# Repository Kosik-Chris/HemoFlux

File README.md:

# HemoFlux
Wearable Photoplethysmography for blood flow analysis.

Example Streaming of Red, Infrared, and green wavelength values to Note 9 Android device:

## Introduction
The Aim of this project is to create a pseudo realtime embedded device for streaming of sensor values to a smart phone or computer (referred to as client).

The device is intended to be placed on patients extremity with premapped PPG node locations and perform sensor fusion for feature extraction focused on determining blood flow and correlated data.

## Implementation

The Primary Mechanism for acheiving this is Bluetooth Low Energy with our embedded device running as the server allowing various clients to connect. The device also supports 2.4GHz wifi for future extensions.

The mobile application is currently implemented through **React Native** (NON EXPO). The Firmware is currently implemented using Arduino Core, with provided SparkFun Library for I2C communication with MAX3010X chips. 

How to install:

Partitioned into 3 segments: board files (easy eda source), ESP32 firmware, Xplat mobile app

### How to install mobile app:

1. Open HemoFlux folder under mobile
2. Install react-native-cli https://www.npmjs.com/package/react-native-cli
3. (recommended) install yarn
4. run npm i/ yarn from root
5. run react-native start from root and react-native run-android
6. Ensure to check your permissions on your phone before running.

### How to install firmware:

1. Open HemoFlux.ino under /firmware/HemoFlux
2. Install I2Cdev as a library
3. **IMPORTANT** currently modified part of the Arduino Core for ESP32 package => BLECharacteristic.cpp. All that is modified is the reversing of the order of bytes set. Will change this in future updates so the client will interpret but this was the "prototype quick solution". The modified file is included in the documents folder.

### Hardware setup

This is (currently) a very very easy project to implement on your breadboard and get working. Additionally, see the schematics under board directory for details.

### Further Aims of this project

1. Animate and annotate a 3D model to realize better blood flow feature extraction

### Current issues/work

1. React Native RAM consumption is dangerously high, performance issues for real time streaming. Performance analysis (starting with code/ algorithm implementation) is the starting point for further work.
2. Fixing working file output/ app local information
3. Implementing feature extraction Matlab work into javascript/ C code
4. Refactoring main BLE streaming into graph code into maintainable format.
5. Continued hardware debugging, currently random disconnects while running firmware.
6. Migration away from Arduino to Espressif, possible migration from React Native to purely native applications.

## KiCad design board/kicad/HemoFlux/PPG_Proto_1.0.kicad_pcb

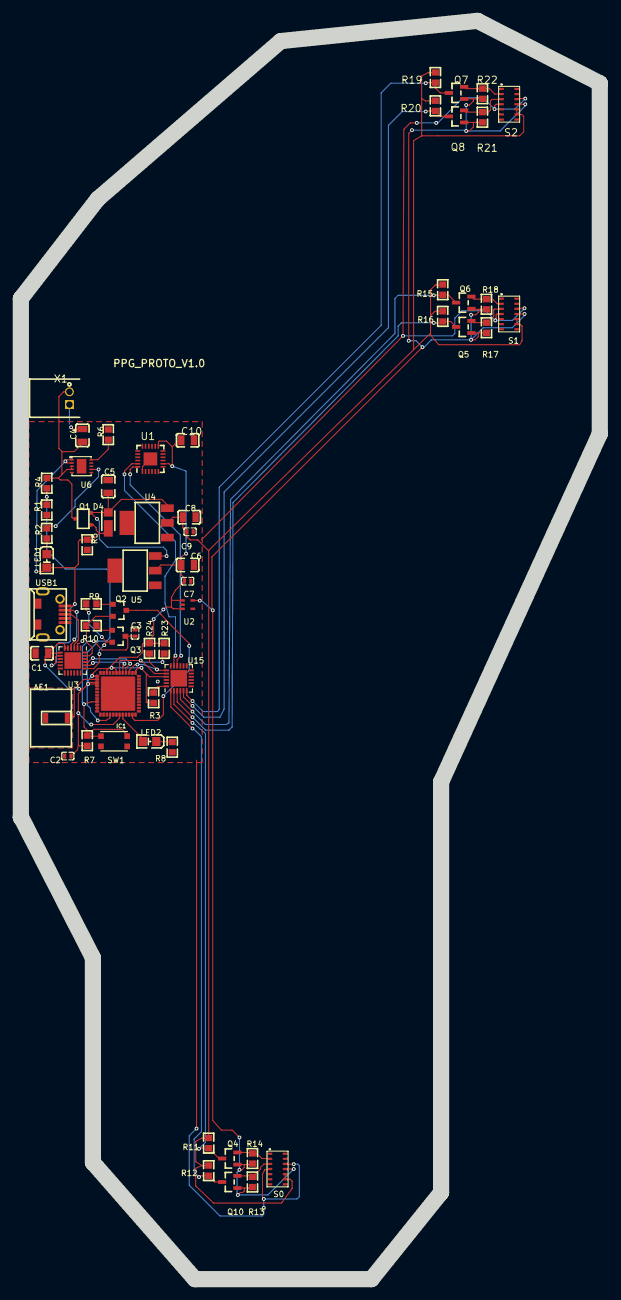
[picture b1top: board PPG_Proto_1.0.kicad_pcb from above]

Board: 2 copper layers, 90.8 x 197.4 mm, 61 parts (0 on the bottom side), 41 nets.

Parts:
AE1: AMCA31-2R450G-S1F-T3; AMCA31-2R450G-S1F-T3.PACK
C1, C4, C5, C6, C8, C10: 10uF; C0805
C2, C3, C7, C9: 1uF; C0402
D4: MBR120; SOD-123HE_L2.8-W1.8-LS3.7-RD
IC1: ESP32-PICO-V4; QFN48
LED1, LED2: SZYY0805YG --GREEN LED; LED0805-R-RD
Q1: DMP2045U-7; SOT-23F
Q2, Q3: MMBT2222ALT1; SOT23-3
Q4, Q5, Q6, Q7, Q8, Q10: 2N7002LT1G; SOT-23_L2.9-W1.3-P0.95-LS2.4-BR
R1, R4, R5: 100K; R0603
R2, R3, R6, R7, R8, R9, R10: 10K; R0603
R11, R12, R13, R14, R15, R16, R17, R18, R19, R20, R21, R22, R23, R24: 4.7K; R0603
S0, S1, S2: MAX30105SMD; OLGA-14
SW1: KMR2; BTN_KMR2_4.6X2.8
U1: MPU6050; QFN50P400X400X95-25T265X275N
U2: TLV70018DCKR; SC70
U3: CP2104; QFN-24-1EP_4X4MM_PITCH0.5MM
U4: ADP3338AKCZ-5-R7; SOT-223
U5: ADP3338AKCZ-3.3RL7; SOT-223
U6: MCP73223-C2SI/MF COPY; TDFN-10_L3.0-W3.0-P0.50-BL-EP
U15: TCA9548A_QFN; QFN-24-1EP_4X4MM_PITCH0.5MM
USB1: MICRO USB 5S B; MICRO-USB-1
X1: S2B-PH-K-S(LF)(SN)

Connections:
+1.8V: Q4.1, Q5.1, Q6.1, Q7.1, Q8.1, Q10.1, R13.2, R14.2, R17.2, R18.2, R21.2, R22.2, S0.11, S1.11, S2.11, U2.5
+3.3V: C1.1, C2.2, C6.1, C7.2, C10.1, IC1.1, IC1.3, IC1.4, IC1.19, IC1.37, IC1.43, IC1.46, R3.1, R7.2, R23.2, R24.2, U1.8, U1.13, U2.1, U2.3, U3.5, U3.6, U3.7, U5.2, U15.21
+5V: C8.2, C9.2, R11.2, R12.2, R15.2, R16.2, R19.2, R20.2, S0.9, S0.10, S1.9, S1.10, S2.9, S2.10, U4.2
BUS_SCL: IC1.39, R24.1, U15.19
BUS_SDA: IC1.42, R23.1, U15.20
D+: U3.3, USB1.3
D-: U3.4, USB1.2
DTR: Q2.2, R10.1, U3.23
GND: C1.2, C2.1, C3.1, C4.1, C5.1, C6.2, C7.1, C8.1, C9.1, C10.2, R1.1, R5.1, R6.1, R8.1, S0.4, S0.12, S1.4, S1.12, S2.4, S2.12, SW1.A, SW1.A', U1.1, U1.9, U1.11, U1.18, U1.25, U2.2, U3.2, U4.1, U5.1, U6.8, U6.9, U6.11, U15.9, U15.18, U15.22, U15.23, USB1.5, X1.1
IO0: IC1.23, Q2.3
IO13: IC1.20, LED2.1
LNA_IN: AE1.S, IC1.2
LV_SCL0: Q4.2, R14.1, S0.2
LV_SCL1: Q6.2, R18.1, S1.2
LV_SCL2: Q7.2, R22.1, S2.2
LV_SDA0: Q10.2, R13.1, S0.3
LV_SDA1: Q5.2, R17.1, S1.3
LV_SDA2: Q8.2, R21.1, S2.3
Q2_1: Q2.1, R9.2
Q3_1: Q3.1, R10.2
R2_1: LED1.2, R2.1
R2_2: R2.2, U6.7
R6_2: R6.2, U6.10
R8_2: LED2.2, R8.2
RESET: C3.2, IC1.9, Q3.3, R7.1, SW1.B, SW1.B'
RTS: Q3.2, R9.1, U3.19
RXD: IC1.40, U3.21
SCL0: Q4.3, R11.1, U15.2
SCL1: Q6.3, R15.1, U15.4
SCL2: Q7.3, R19.1, U15.6
SCL7: U1.23, U15.17
SDA0: Q10.3, R12.1, U15.1
SDA1: Q5.3, R16.1, U15.3
SDA2: Q8.3, R20.1, U15.5
SDA7: U1.24, U15.16
TXD: IC1.41, U3.20
U15_24: R3.2, U15.24
VBAT: C4.2, Q1.3, R4.2, U6.3, U6.4, X1.2
VBAT_REC: C5.2, D4.2, Q1.2, U4.3, U5.3
VBAT_SENSE: IC1.16, R1.2, R4.1
VBUS: D4.1, LED1.1, Q1.1, R5.2, U3.8, U6.1, U6.2, USB1.1

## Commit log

2020-02-24 Init
2020-02-24 Hardware files upload
2020-02-24 Swap over misc sketches into central repo
2020-02-24 Working App update. TODO (x2): 1. Acquire and measure BLE readings 2. Test on ios/ that yarn is working for node env
2020-03-06 Android Icon update
2020-03-08 Working on BLE ingest
2020-03-09 Firmware + BLE tx updates. Removed RTOS from PPG sys as unstable/ dropping of tasks. PPG_SYS.ino is main firmware file. App in basic receive functionality with UI rendering for 1 characteristic
2020-03-09 Added battery tx and changed pin to ADC1 GPIO 34
2020-03-11 IOS updates
2020-03-18 New Board design. Updated documentation.
2020-03-19 Mobile app render single line graph value. Determined timing sensitivities for UI response requires lower frequency update rates to notifications. Active firmware is HemoFlux, not PPG RTOS. TODO: upd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
2020-03-20 variable ppg support. IMU in progress. Exception handling
2020-03-23 Firmware updates: Added IMU calibration, BLE broadcasting. Updated channel BLE services to single channel service vs. service for each wavelength TODO: fix endianess of the BLE transmission (backward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
2020-03-26 HR start + more imu calibration IMU calibrates consistenyl below 13s. Acceptable for now
2020-03-26 Updated MATLAB files
2020-03-26 Changed Spo2 formula
    Added Spo2 formula derived from test data
2020-03-28 Descriptor update for BLE notify.
2020-03-28 IMU state handling updated. quick and dirty
2020-03-31 Single PPG, 3 channel real time graph update. Raw data values respond well at around 33ms max update (throughput as well). JSON file updated with uC header system variables. TODO: huge incoming UI/UX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
2020-03-31 Turned RawDataStream into Component. Untested support for up to 7 PPG
2020-04-01 npm update
2020-04-02 Fixed X axis gooberness - FPS issues if trying massive moving timeline. Still internally recorded for Db/ csv etc. In progress: react-navigation/native upgrade from current stack navigation. UI overh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
2020-04-02 Updated dependacy: utilizing react-navigation V4.0 API NOT V5.0
2020-04-03 Temporary/ Feature showcase 3D model + gradle fixes. Added Tab navigator In progress: Stack Navigator per each pane, splashscreen, Recording and local storage, continued UI development, adding "sessi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
2020-04-06 Splash Screen update.
2020-04-06 IOS update, swift 5 switch
2020-04-07 IOS, working on permissions error in RNpermissions + building. Removed date picker.
2020-04-07 Firmware config.
2020-04-08 UI updates. Added info screen, Fixed BLE mounting error. TODO(in order): get IOS working Finalize the Help me/ info screens Finalize the session how to screen (when not started)\ Implement device sto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
2020-04-08 header UI fix
2020-04-09 IOS build options config
2020-04-09 IOS officially working! Major performance limitations compared to android Note 9 vs I6. JS thread looks overburdened by Array shifting.
2020-04-09 HRStream start + various UI. firmware added HRValue broadcast
2020-04-09 Android FS test working
2020-04-09 IOS FS test working
2020-04-09 merge
2020-04-09 double declare on merge :/
2020-04-09 Adding mail functionality. File IO requires async.
2020-04-09 Email working android, works utilizing external storage.
2020-04-09 IOS working email data export
2020-04-09 Insight
2020-04-10 Insights updates
2020-04-12 Beta 0.1.1 Android release.
2020-05-26 header update
2020-05-26 readme updates
2020-05-26 readme, image updates
